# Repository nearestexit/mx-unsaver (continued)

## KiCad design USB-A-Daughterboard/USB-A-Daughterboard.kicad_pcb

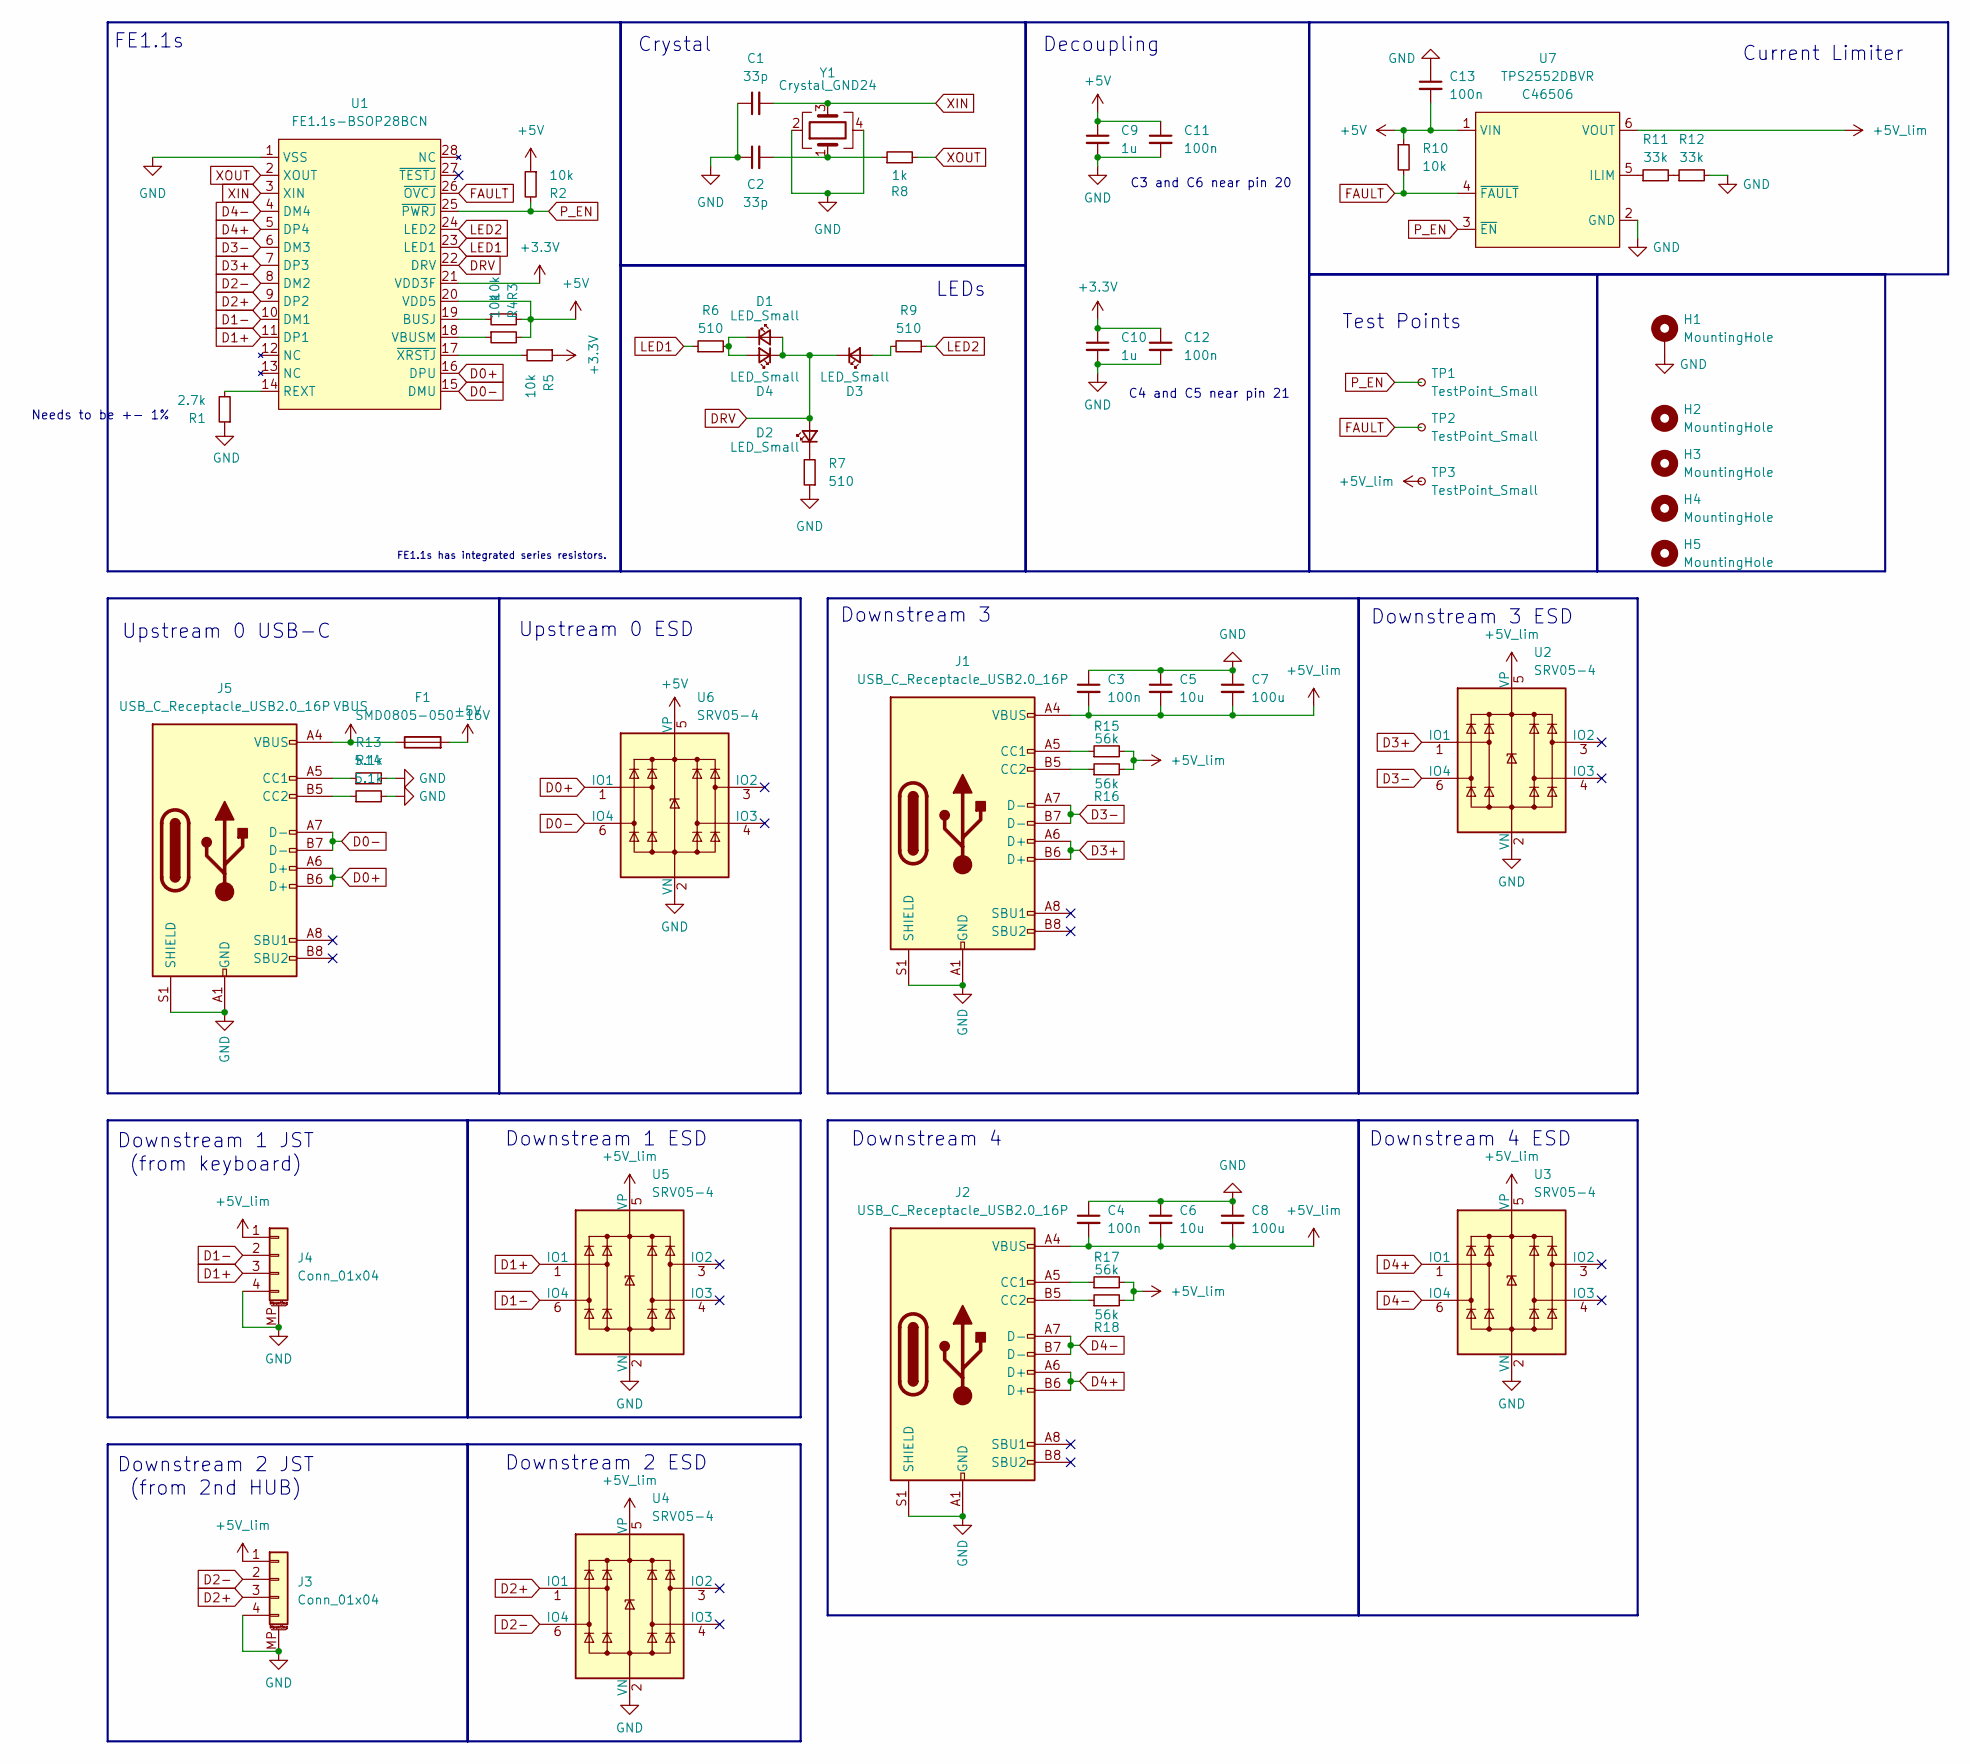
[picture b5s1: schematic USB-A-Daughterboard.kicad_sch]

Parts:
C1, C2: 33p; C_0603_1608Metric; Digikey 1276-1070-1-ND
C3, C4, C11, C12, C13: 100n; C_0603_1608Metric; Digikey 311-1088-1-ND
C5, C6: 10u; C_0603_1608Metric; Digikey 1276-1192-1-ND
C7, C8: 100u; C_1206_3216Metric; Digikey 490-GRM31CR60J107KEA8LCT-ND
C9, C10: 1u; C_0603_1608Metric; Digikey 1276-6524-1-ND
D1, D2, D3, D4: LED_Small; LED_0603_1608Metric; Digikey 2007-BL-HJC36G-AV-TRBCT-ND
F1: SMD0805-050-16V; Fuse_1206_3216Metric; Manufacturer Part Number SMD0805-050-16V; LCSC Part Number C2833485
H1: MountingHole; MountingHole_2.7mm_M2.5_DIN965_Pad
H2, H3, H4, H5: MountingHole; MountingHole_2.7mm_M2.5
J1, J2, J5: USB_C_Receptacle_USB2.0_16P; PHOENIX_1332645; Digikey 277-1332645CT-ND
J3, J4: Conn_01x04; JST_SH_SM04B-SRSS-TB_1x04-1MP_P1.00mm_Horizontal; Digikey 455-SM04B-SRSS-TBCT-ND
R1: 2.7k; R_0603_1608Metric; Digikey RMCF0603FT2K70
R2, R3, R4, R5, R10: 10k; R_0603_1608Metric; Digikey 311-10.0KHRCT-ND
R6, R7, R9: 510; R_0603_1608Metric; Digikey RR08P510DCT-ND
R8: 1k; R_0603_1608Metric; Digikey RMCF0603FT1K00CT-ND
R11, R12: 33k; R_0603_1608Metric; Digikey 311-33.0KHRCT-ND
R13, R14: 5.1k; R_0603_1608Metric; Digikey P5.10KHCT-ND
R15, R16, R17, R18: 56k; R_0603_1608Metric; Digikey P56KGCT-ND
TP1, TP2, TP3: TestPoint_Small; TestPoint_THTPad_D1.0mm_Drill0.5mm
U1: FE1.1s-BSOP28BCN; SSOP-28_3.9x9.9mm_P0.635mm
U2, U3, U4, U5, U6: SRV05-4; SOT-23-6-routable; Digikey 5399-SRV05-4CT-ND
U7: TPS2552DBVR; SOT-23-6; LCSC C46506
Y1: Crystal_GND24; Crystal_SMD_3225-4Pin_3.2x2.5mm; Digikey XC1810CT-ND

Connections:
+3.3V: C10.1, C12.1, R5.1, U1.21 (VDD3F)
+5V: C9.1, C11.1, C13.2, F1.2, R2.1, R3.2, R4.2, R10.1, U1.20 (VDD5), U6.5 (VP), U7.1 (VIN)
+5V_lim: C3.2, C4.2, C5.2, C6.2, C7.2, C8.2, J1.A4 (VBUS), J1.A9 (VBUS), J1.B4 (VBUS), J1.B9 (VBUS), J2.A4 (VBUS), J2.A9 (VBUS), J2.B4 (VBUS), J2.B9 (VBUS), J3.1, J4.1, R15.2, R16.2, R17.2, R18.2, TP3.1, U2.5 (VP), U3.5 (VP), U4.5 (VP), U5.5 (VP), U7.6 (VOUT)
D0+: J5.A6 (D+), J5.B6 (D+), U1.16 (DPU), U6.1 (IO1)
D0-: J5.A7 (D-), J5.B7 (D-), U1.15 (DMU), U6.6 (IO4)
D1+: J4.3, U1.11 (DP1), U5.1 (IO1)
D1-: J4.2, U1.10 (DM1), U5.6 (IO4)
D2+: J3.3, U1.9 (DP2), U4.1 (IO1)
D2-: J3.2, U1.8 (DM2), U4.6 (IO4)
D3+: J1.A6 (D+), J1.B6 (D+), U1.7 (DP3), U2.1 (IO1)
D3-: J1.A7 (D-), J1.B7 (D-), U1.6 (DM3), U2.6 (IO4)
D4+: J2.A6 (D+), J2.B6 (D+), U1.5 (DP4), U3.1 (IO1)
D4-: J2.A7 (D-), J2.B7 (D-), U1.4 (DM4), U3.6 (IO4)
DRV: D1.2 (A), D2.2 (A), D3.1 (K), D4.1 (K), U1.22 (DRV)
FAULT: R10.2, TP2.1, U1.26 (~OVCJ), U7.4 (~FAULT)
GND: C1.1, C2.1, C3.1, C4.1, C5.1, C6.1, C7.1, C8.1, C9.2, C10.2, C11.2, C12.2, C13.1, H1.1, J1.A1 (GND), J1.A12 (GND), J1.B1 (GND), J1.B12 (GND), J1.S1 (SHIELD), J2.A1 (GND), J2.A12 (GND), J2.B1 (GND), J2.B12 (GND), J2.S1 (SHIELD), J3.4, J3.MP (MountPin), J4.4, J4.MP (MountPin), J5.A1 (GND), J5.A12 (GND), J5.B1 (GND), J5.B12 (GND), J5.S1 (SHIELD), R1.1, R7.1, R12.2, R13.2, R14.2, U1.1 (VSS), U2.2 (VN), U3.2 (VN), U4.2 (VN), U5.2 (VN), U6.2 (VN), U7.2 (GND), Y1.2, Y1.4
LED1: R6.1, U1.23 (LED1)
LED2: R9.1, U1.24 (LED2)
unnamed: C2.2, R8.1, Y1.1
unnamed: D1.1 (K), D4.2 (A), R6.2
unnamed: D2.1 (K), R7.2
unnamed: D3.2 (A), R9.2
unnamed: J1.A5 (CC1), R15.1
unnamed: J1.B5 (CC2), R16.1
unnamed: J2.A5 (CC1), R17.1
unnamed: J2.B5 (CC2), R18.1
unnamed: J5.A5 (CC1), R13.1
unnamed: J5.B5 (CC2), R14.1
unnamed: R11.2, R12.1
unnamed: R3.1, U1.19 (BUSJ)
unnamed: R1.2, U1.14 (REXT)
unnamed: R4.1, U1.18 (VBUSM)
unnamed: R5.2, U1.17 (~XRSTJ)
unnamed: R11.1, U7.5 (ILIM)
P_EN: R2.2, TP1.1, U1.25 (~PWRJ), U7.3 (~EN)
VBUS: F1.1, J5.A4 (VBUS), J5.A9 (VBUS), J5.B4 (VBUS), J5.B9 (VBUS)
XIN: C1.2, U1.3 (XIN), Y1.3
XOUT: R8.2, U1.2 (XOUT)

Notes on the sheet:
Upstream 0 USB-C
FE1.1s
C3 and C6 near pin 20
C4 and C5 near pin 21
Downstream 1 JST
Test Points
Crystal
Decoupling
(from 2nd HUB)
Downstream 3 ESD
Downstream 4
(from keyboard)
Downstream 4 ESD
Needs to be +- 1%
Downstream 2 ESD
FE1.1s has integrated series resistors.
LEDs
Downstream 1 ESD
Current Limiter
Downstream 2 JST
Downstream 3
Upstream 0 ESD

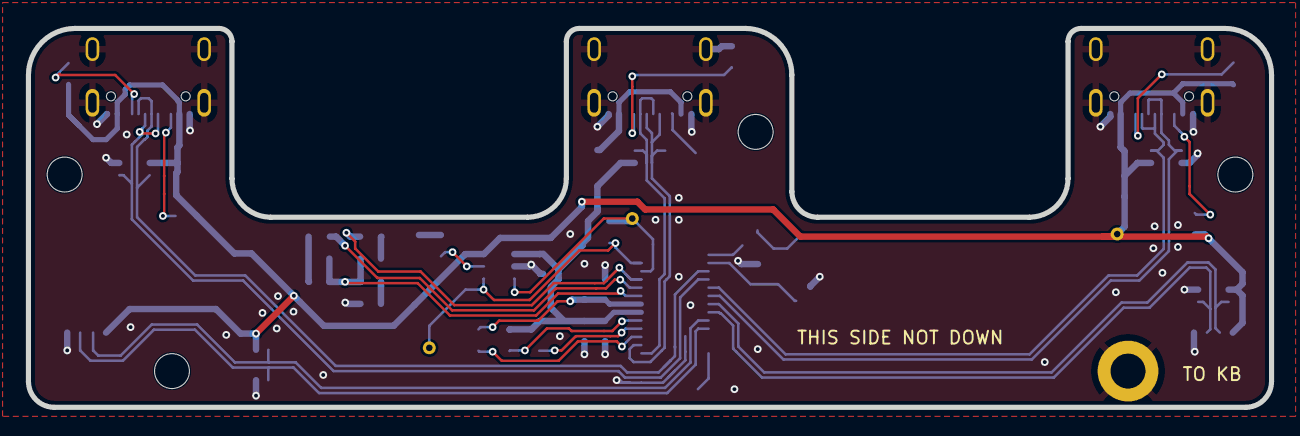
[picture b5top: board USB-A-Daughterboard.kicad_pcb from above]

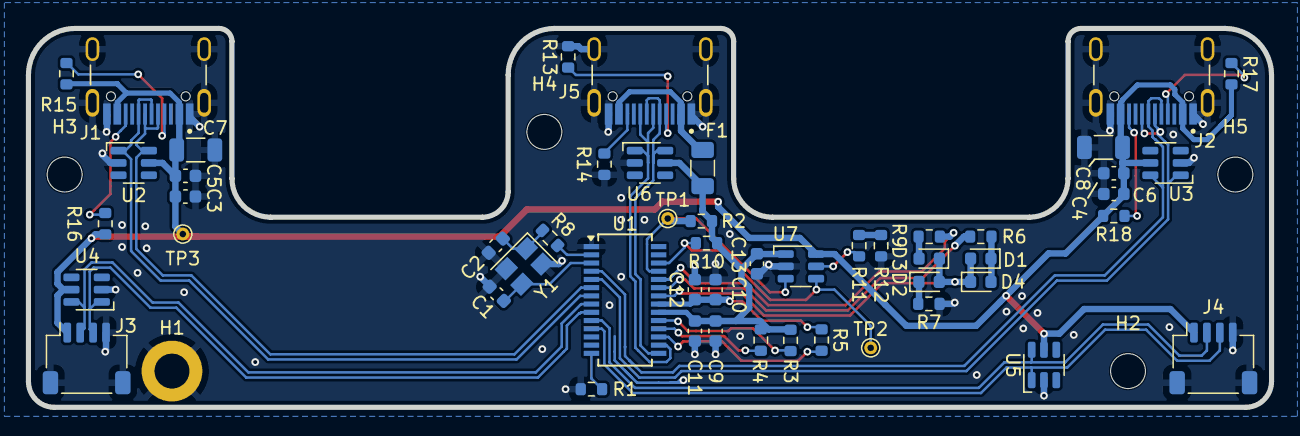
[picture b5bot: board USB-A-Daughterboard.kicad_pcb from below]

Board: 2 copper layers, 96.1 x 29.3 mm, 57 parts (57 on the bottom side), 38 nets.

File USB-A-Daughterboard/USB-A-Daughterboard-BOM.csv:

Reference,Value,Datasheet,Footprint,Qty,DNP,Digikey
"C1,C2",33p,~,Capacitor_SMD:C_0603_1608Metric,2,,1276-1070-1-ND
"C3,C4,C11,C12,C13",100n,~,Capacitor_SMD:C_0603_1608Metric,5,,311-1088-1-ND
"C5,C6",10u,~,Capacitor_SMD:C_0603_1608Metric,2,,1276-1192-1-ND
"C7,C8",100u,~,Capacitor_SMD:C_1206_3216Metric,2,,490-GRM31CR60J107KEA8LCT-ND
"C9,C10",1u,~,Capacitor_SMD:C_0603_1608Metric,2,,1276-6524-1-ND
"D1,D2,D3,D4",LED_Small,~,LED_SMD:LED_0603_1608Metric,4,,2007-BL-HJC36G-AV-TRBCT-ND
F1,SMD0805-050-16V,~,Fuse:Fuse_1206_3216Metric,1,,18-1206L050/24WRCT-ND
"J1,J2,J5",USB_C_Receptacle_USB2.0_16P,https://www.usb.org/sites/default/files/documents/usb_type-c.zip,mx-unsaver:PHOENIX_1332645,3,,277-1332645CT-ND
"J3,J4",Conn_01x04,~,Connector_JST:JST_SH_SM04B-SRSS-TB_1x04-1MP_P1.00mm_Horizontal,2,,455-SM04B-SRSS-TBCT-ND
R1,2.7k,~,Resistor_SMD:R_0603_1608Metric,1,,RMCF0603FT2K70
"R2,R3,R4,R5,R10",10k,~,Resistor_SMD:R_0603_1608Metric,5,,311-10.0KHRCT-ND
"R6,R7,R9",510,~,Resistor_SMD:R_0603_1608Metric,3,,RR08P510DCT-ND
R8,1k,~,Resistor_SMD:R_0603_1608Metric,1,,RMCF0603FT1K00CT-ND
"R11,R12",33k,~,Resistor_SMD:R_0603_1608Metric,2,,311-33.0KHRCT-ND 
"R13,R14",5.1k,~,Resistor_SMD:R_0603_1608Metric,2,,P5.10KHCT-ND
"R15,R16,R17,R18",56k,~,Resistor_SMD:R_0603_1608Metric,4,,P56KGCT-ND
"TP1,TP2,TP3",TestPoint_Small,~,TestPoint:TestPoint_THTPad_D1.0mm_Drill0.5mm,3,,
U1,FE1.1s-BSOP28BCN,https://www.lcsc.com/datasheet/C9359.pdf,Package_SO:SSOP-28_3.9x9.9mm_P0.635mm,1,,
"U2,U3,U4,U5,U6",SRV05-4,http://www.onsemi.com/pub/Collateral/SRV05-4-D.PDF,PCM_marbastlib-various:SOT-23-6-routable,5,,5399-SRV05-4CT-ND
U7,TPS2552DBVR,,Package_TO_SOT_SMD:SOT-23-6,1,,
Y1,Crystal_GND24,~,Crystal:Crystal_SMD_3225-4Pin_3.2x2.5mm,1,,XC1810CT-ND

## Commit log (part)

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2026-01-19 Add Files
